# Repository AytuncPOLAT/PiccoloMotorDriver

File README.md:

# PiccoloMotorDriver

Yet another open source servo motor driver designed using Kicad, based on STM32H723 MCU and DRV8316 integrated 3-phase motor driver.

Firmware can be found here (under development): https://github.com/AytuncPOLAT/PiccoloMotorDriverFw

All the subsystems have been tested

| Subsystem     | Test Status           |
| ---------     | ------------------    |
| FDCAN         | :heavy_check_mark:    |
| RS485         | :heavy_check_mark:    |
| USB           | :heavy_check_mark:    |
| Debug UART    | :clock9:              |
| SWD           | :heavy_check_mark:    |
| Ext. Encoder  | :heavy_check_mark:    |
| Ext. Analog   | :heavy_check_mark:    |
| LEDs          | :heavy_check_mark:    |
| J9 GPIOs      | :clock9:              |
| DRV8316       | :heavy_check_mark:    |

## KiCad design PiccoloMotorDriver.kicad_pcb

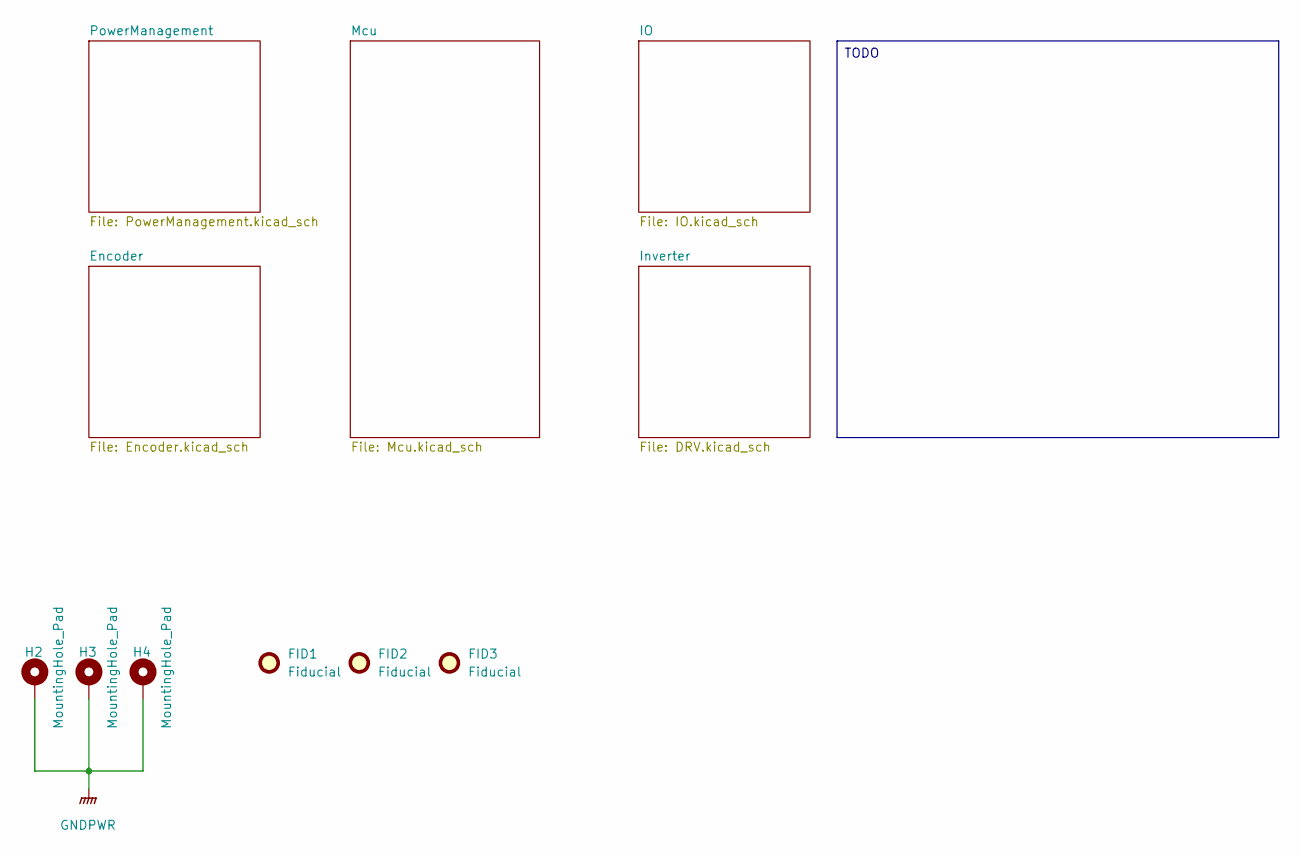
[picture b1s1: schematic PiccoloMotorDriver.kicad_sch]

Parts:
FID1, FID2, FID3: Fiducial; Fiducial_0.5mm_Mask1mm
H2, H3, H4: MountingHole_Pad; MountingHole_3.2mm_M3_Pad_Via

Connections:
GND: H2.1 (1_1), H3.1 (1_1), H4.1 (1_1); also elsewhere on the board

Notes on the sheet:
TODO

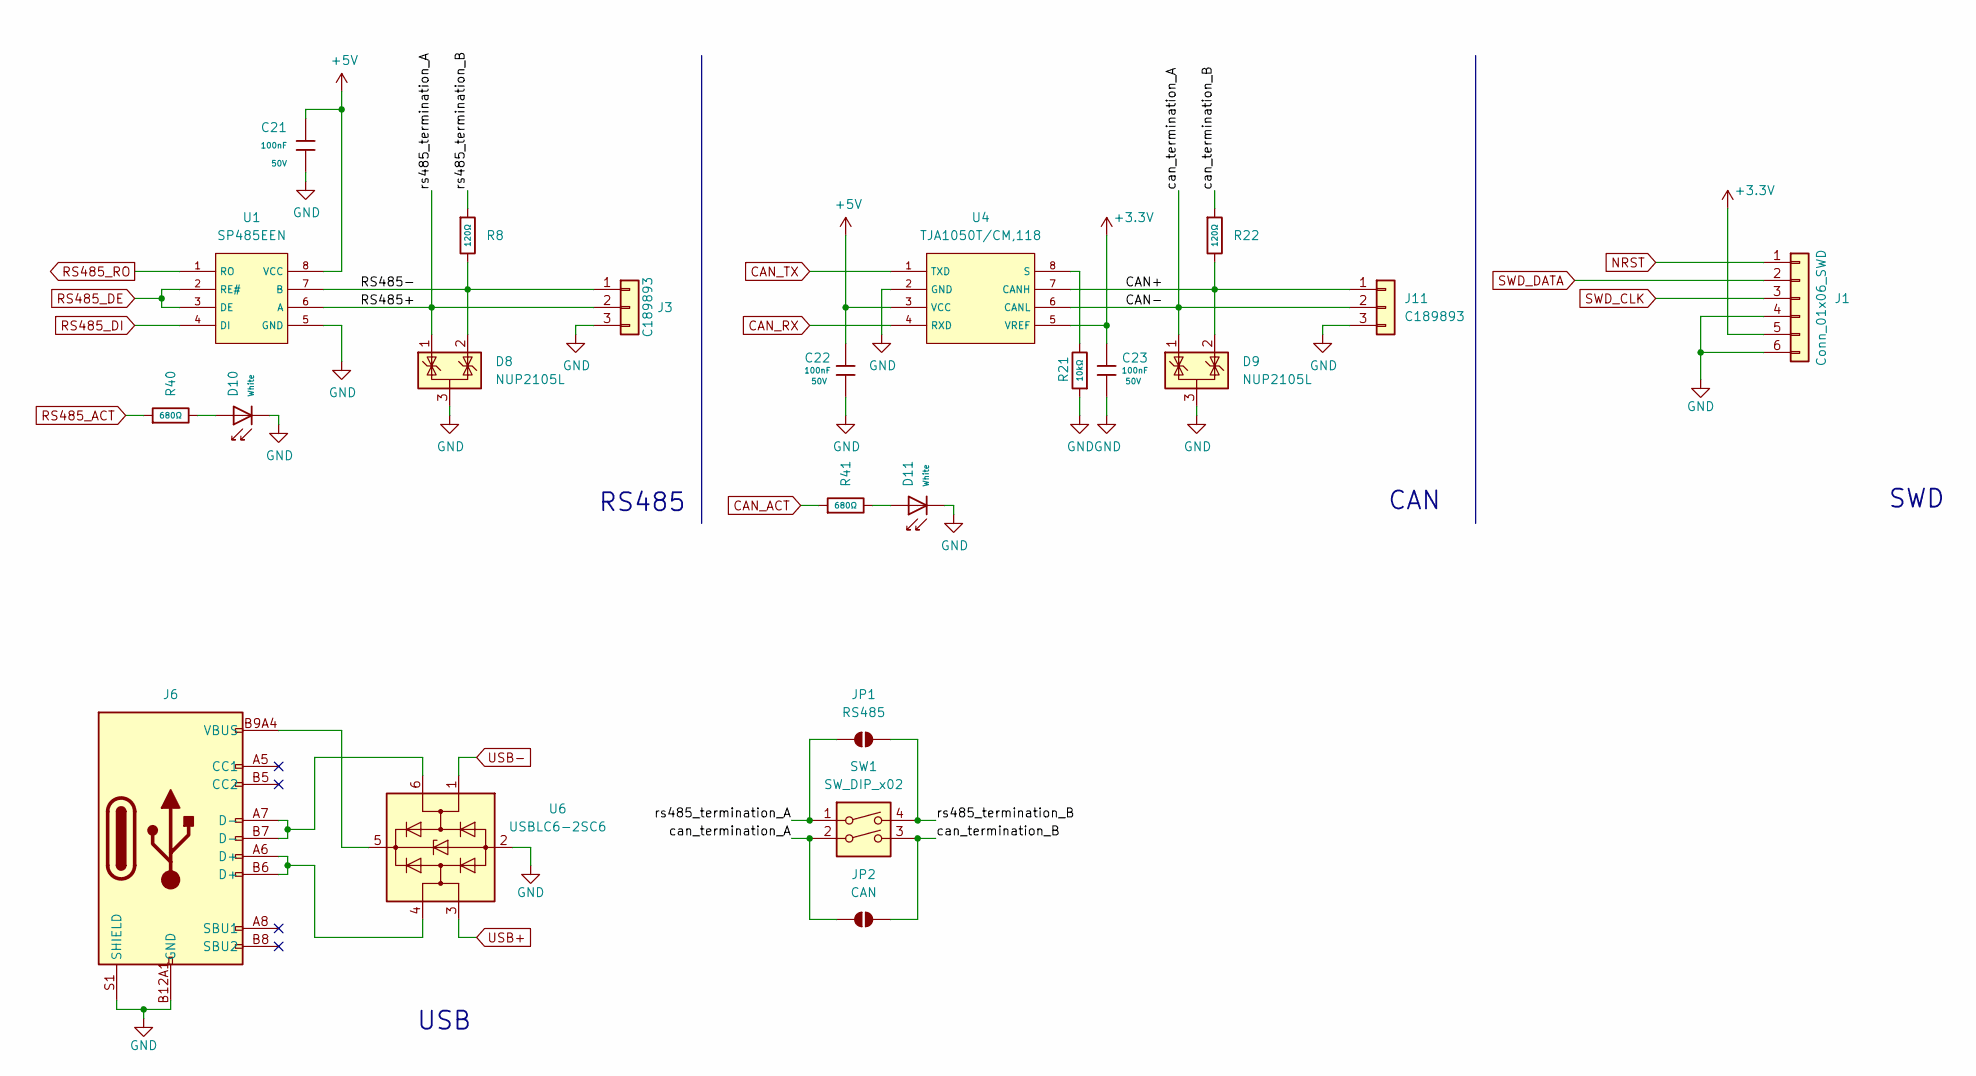
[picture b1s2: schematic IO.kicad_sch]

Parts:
C21, C22, C23: 100nF; C_0603; Voltage Rated 50V; Tolerance ±10%; Part CC0603KRX7R9BB104; LCSC C14663
D8, D9: NUP2105L; SOT-23; LCSC C14486
D10, D11: White; D_0603; Part KT-0603W; LCSC C2290
J1: Conn_01x06_SWD; JST_GH_SM05B-GHS-TB_1x05-1MP_P1.25mm_Horizontal; LCSC C189896
J3, J11: C189893; JST_GH_SM02B-GHS-TB_1x02-1MP_P1.25mm_Horizontal; LCSC C189893
J6: Connector, USB-TYPE-C-16P; TYPE-C-SMD_HX-TYPE-C-16PIN; LCSC C2927039
JP1: RS485; SolderJumper-2_P1.3mm_Open_TrianglePad1.0x1.5mm
JP2: CAN; SolderJumper-2_P1.3mm_Open_TrianglePad1.0x1.5mm
R8, R22: 120Ω; R_0603; Overload Voltage (Max) 75V; Tolerance ±1%; Part 0603WAF1200T5E; LCSC C22787
R21: 10kΩ; R_0603; Overload Voltage (Max) 75V; Tolerance ±1%; Part 0603WAF1002T5E; LCSC C25804
R40, R41: 680Ω; R_0603; Overload Voltage (Max) 75V; Tolerance ±1%; Part 0603WAF6800T5E; LCSC C23228
SW1: SW_DIP_x02; SMDIP-4_W7.62mm; LCSC C6331180
U1: SP485EEN; SOIC-8_L5.0-W4.0-P1.27-LS6.0-BL; Supply Voltage 4.75V~5.25V; Part SP485EEN-L/TR; LCSC C6855
U4: TJA1050T/CM,118; SOIC-8_L5.0-W4.0-P1.27-LS6.0-BL; Supply Voltage 4.75V~5.25V; Part TJA1050T/CM,118; LCSC C6952
U6: USBLC6-2SC6; SOT-23-6; LCSC C5261088

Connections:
+3.3V: C23.1, J1.5, U4.5 (VREF); also elsewhere on the board
+5V: C21.1, C22.1, U1.8 (VCC), U4.3 (VCC); also elsewhere on the board
/IO/CAN+: D9.2 (K), J11.1, R22.2, U4.7 (CANH)
/IO/CAN-: D9.1 (K), J11.2, JP2.1 (A), SW1.2, U4.6 (CANL)
/IO/RS485+: D8.1 (K), J3.2, JP1.2 (B), SW1.1, U1.6 (A)
/IO/RS485-: D8.2 (K), J3.1, R8.2, U1.7 (B)
/IO/can_termination_B: JP2.2 (B), R22.1, SW1.3
/IO/rs485_termination_B: JP1.1 (A), R8.1, SW1.4
CAN_ACT: R41.1; also elsewhere on the board
CAN_RX: U4.4 (RXD); also elsewhere on the board
CAN_TX: U4.1 (TXD); also elsewhere on the board
GND: C21.2, C22.2, C23.2, D8.3 (A), D9.3 (A), D10.1, D11.1, J1.4, J1.6, J3.3, J6.A12B1 (GND), J6.B12A1 (GND), J6.S1 (SHIELD), J11.3, R21.1, U1.5 (GND), U4.2 (GND), U6.2 (GND); also elsewhere on the board
NRST: J1.1; also elsewhere on the board
unnamed: D10.2, R40.2
unnamed: D11.2, R41.2
unnamed: J6.A6 (D+), J6.B6 (D+), U6.4 (I/O2)
unnamed: J6.A7 (D-), J6.B7 (D-), U6.6 (I/O1)
unnamed: R21.2, U4.8 (S)
unnamed: J6.A9B4 (VBUS), J6.B9A4 (VBUS), U6.5 (VBUS)
RS485_ACT: R40.1; also elsewhere on the board
RS485_DE: U1.2 (RE#), U1.3 (DE); also elsewhere on the board
RS485_DI: U1.4 (DI); also elsewhere on the board
RS485_RO: U1.1 (RO); also elsewhere on the board
SWD_CLK: J1.3; also elsewhere on the board
SWD_DATA: J1.2; also elsewhere on the board
USB+: U6.3 (I/O2); also elsewhere on the board
USB-: U6.1 (I/O1); also elsewhere on the board

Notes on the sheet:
RS485
USB
SWD
CAN

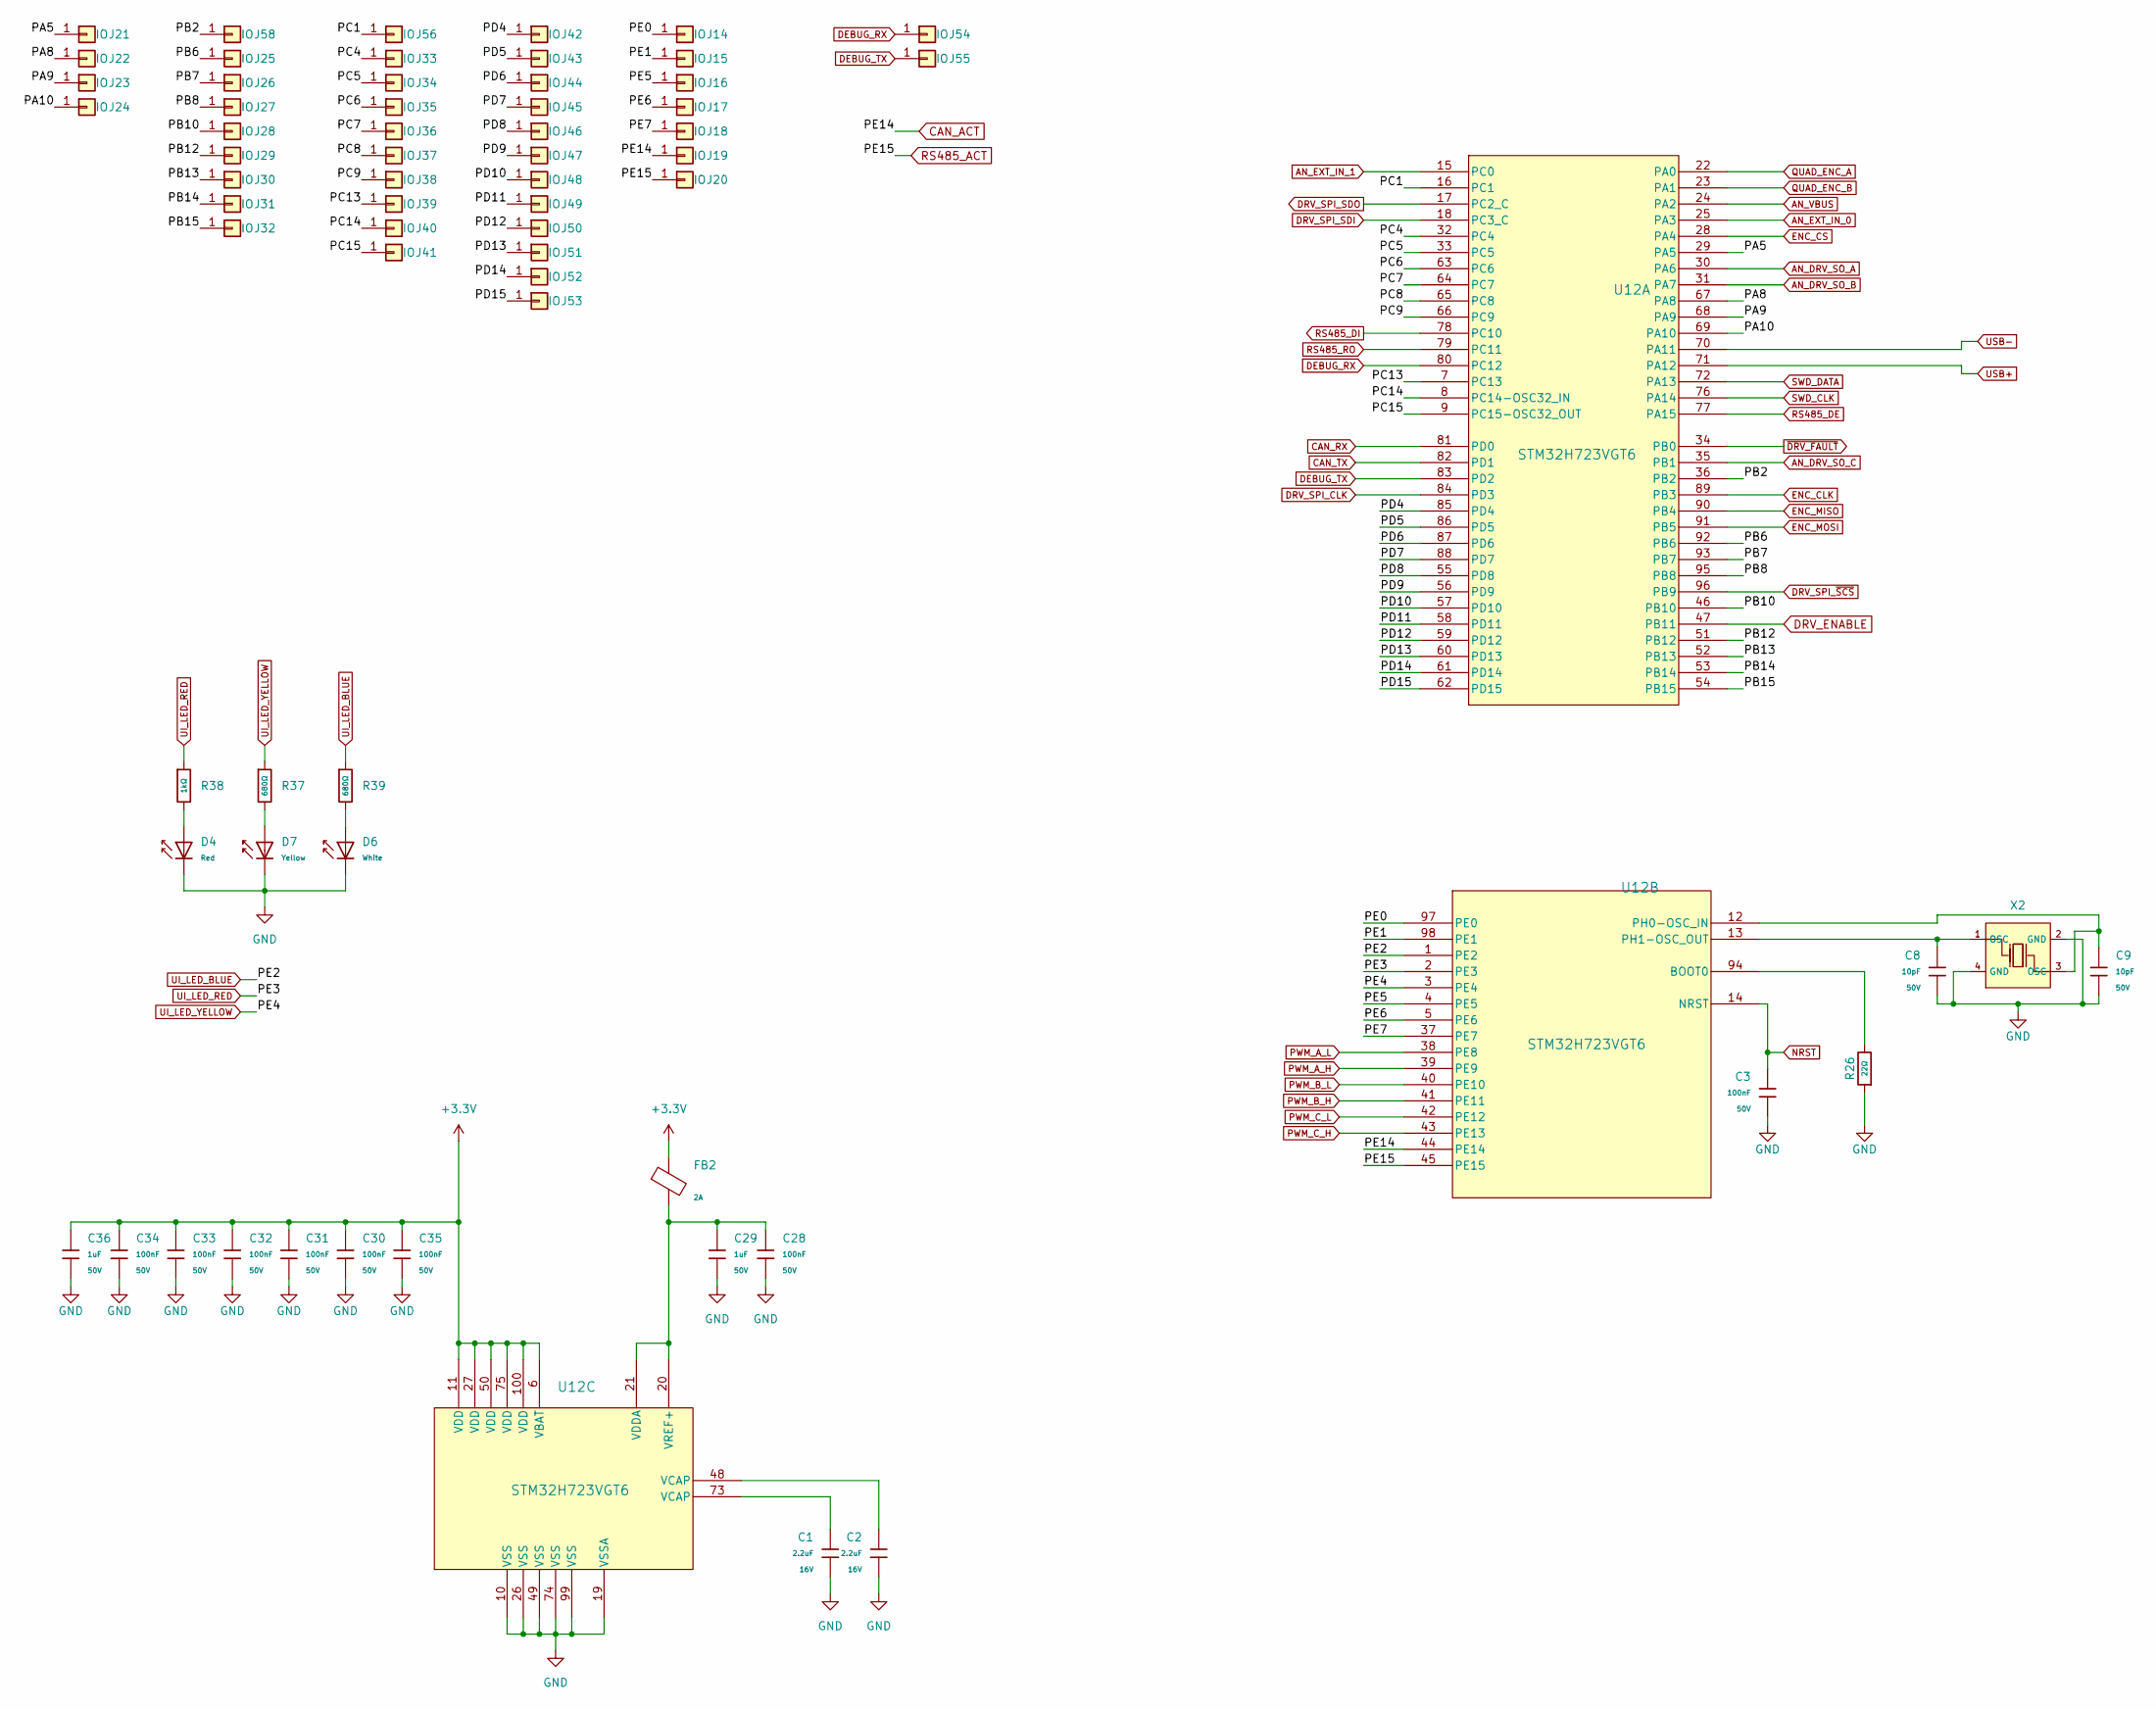
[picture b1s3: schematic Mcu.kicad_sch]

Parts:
C1, C2: 2.2uF; C_0603; Voltage Rated 16V; Tolerance ±10%; Part CL10A225KO8NNNC; LCSC C23630
C3, C28, C30, C31, C32, C33, C34, C35: 100nF; C_0603; Voltage Rated 50V; Tolerance ±10%; Part CC0603KRX7R9BB104; LCSC C14663
C8, C9: 10pF; C_0603; Voltage Rated 50V; Tolerance ±5%; Part CL10C100JB8NNNC; LCSC C1634
C29, C36: 1uF; C_0603; Voltage Rated 50V; Tolerance ±10%; Part CL10A105KB8NNNC; LCSC C15849
D4: Red; D_0603; Part KT-0603R; LCSC C2286
D6: White; D_0603; Part KT-0603W; LCSC C2290
D7: Yellow; D_0603; Forward Voltage (VF) 1.6V~2.6V; Part NCD0603Y2; LCSC C89811
FB2: FB_0603; Current Rating 2A; Tolerance ±25%; Part BLM18PG121SN1D; LCSC C14709
J14, J15, J16, J17, J18, J19, J20, J21, J22, J23, J24, J25, J26, J27, J28, J29, J30, J31, J32, J33, J34, J35, J36, J37, J38, J39, J40, J41, J42, J43, J44, J45, J46, J47, J48, J49, J50, J51, J52, J53, J54, J55, J56, J58: IO; TestPoint_THTPad_D1.0mm_Drill0.5mm
R26: 22Ω; R_0603; Overload Voltage (Max) 75V; Tolerance ±1%; Part 0603WAF220JT5E; LCSC C23345
R37, R39: 680Ω; R_0603; Overload Voltage (Max) 75V; Tolerance ±1%; Part 0603WAF6800T5E; LCSC C23228
R38: 1kΩ; R_0603; Overload Voltage (Max) 75V; Tolerance ±1%; Part 0603WAF1001T5E; LCSC C21190
U12: STM32H723VGT6; LQFP-100_14x14mm_P0.5mm; LCSC C730142
X2: X322516MLB4SI; OSC-SMD_4P-L3.2-W2.5-BL; Frequency Tolerance ±10ppm; Part X322516MLB4SI; LCSC C13738

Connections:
+3.3V: C30.1, C31.1, C32.1, C33.1, C34.1, C35.1, C36.1, FB2.1, U12.6 (VBAT), U12.11 (VDD), U12.27 (VDD), U12.50 (VDD), U12.75 (VDD), U12.100 (VDD); also elsewhere on the board
/Mcu/PA5: J21.1 (Pin_1_1), U12.29 (PA5)
/Mcu/PA8: J22.1 (Pin_1_1), U12.67 (PA8)
/Mcu/PA9: J23.1 (Pin_1_1), U12.68 (PA9)
/Mcu/PA10: J24.1 (Pin_1_1), U12.69 (PA10)
/Mcu/PB2: J58.1 (Pin_1_1), U12.36 (PB2)
/Mcu/PB6: J25.1 (Pin_1_1), U12.92 (PB6)
/Mcu/PB7: J26.1 (Pin_1_1), U12.93 (PB7)
/Mcu/PB8: J27.1 (Pin_1_1), U12.95 (PB8)
/Mcu/PB10: J28.1 (Pin_1_1), U12.46 (PB10)
/Mcu/PB12: J29.1 (Pin_1_1), U12.51 (PB12)
/Mcu/PB13: J30.1 (Pin_1_1), U12.52 (PB13)
/Mcu/PB14: J31.1 (Pin_1_1), U12.53 (PB14)
/Mcu/PB15: J32.1 (Pin_1_1), U12.54 (PB15)
/Mcu/PC1: J56.1 (Pin_1_1), U12.16 (PC1)
/Mcu/PC4: J33.1 (Pin_1_1), U12.32 (PC4)
/Mcu/PC5: J34.1 (Pin_1_1), U12.33 (PC5)
/Mcu/PC6: J35.1 (Pin_1_1), U12.63 (PC6)
/Mcu/PC7: J36.1 (Pin_1_1), U12.64 (PC7)
/Mcu/PC8: J37.1 (Pin_1_1), U12.65 (PC8)
/Mcu/PC9: J38.1 (Pin_1_1), U12.66 (PC9)
/Mcu/PC13: J39.1 (Pin_1_1), U12.7 (PC13)
/Mcu/PC14: J40.1 (Pin_1_1), U12.8 (PC14-OSC32_IN)
/Mcu/PC15: J41.1 (Pin_1_1), U12.9 (PC15-OSC32_OUT)
/Mcu/PD4: J42.1 (Pin_1_1), U12.85 (PD4)
/Mcu/PD5: J43.1 (Pin_1_1), U12.86 (PD5)
/Mcu/PD6: J44.1 (Pin_1_1), U12.87 (PD6)
/Mcu/PD7: J45.1 (Pin_1_1), U12.88 (PD7)
/Mcu/PD8: J46.1 (Pin_1_1), U12.55 (PD8)
/Mcu/PD9: J47.1 (Pin_1_1), U12.56 (PD9)
/Mcu/PD10: J48.1 (Pin_1_1), U12.57 (PD10)
/Mcu/PD11: J49.1 (Pin_1_1), U12.58 (PD11)
/Mcu/PD12: J50.1 (Pin_1_1), U12.59 (PD12)
/Mcu/PD13: J51.1 (Pin_1_1), U12.60 (PD13)
/Mcu/PD14: J52.1 (Pin_1_1), U12.61 (PD14)
/Mcu/PD15: J53.1 (Pin_1_1), U12.62 (PD15)
/Mcu/PE0: J14.1 (Pin_1_1), U12.97 (PE0)
/Mcu/PE1: J15.1 (Pin_1_1), U12.98 (PE1)
/Mcu/PE5: J16.1 (Pin_1_1), U12.4 (PE5)
/Mcu/PE6: J17.1 (Pin_1_1), U12.5 (PE6)
/Mcu/PE7: J18.1 (Pin_1_1), U12.37 (PE7)
AN_DRV_SO_A: U12.30 (PA6); also elsewhere on the board
AN_DRV_SO_B: U12.31 (PA7); also elsewhere on the board
AN_DRV_SO_C: U12.35 (PB1); also elsewhere on the board
AN_EXT_IN_0: U12.25 (PA3); also elsewhere on the board
AN_EXT_IN_1: U12.15 (PC0); also elsewhere on the board
AN_VBUS: U12.24 (PA2); also elsewhere on the board
CAN_ACT: J19.1 (Pin_1_1), U12.44 (PE14); also elsewhere on the board
CAN_RX: U12.81 (PD0); also elsewhere on the board
CAN_TX: U12.82 (PD1); also elsewhere on the board
DEBUG_RX: J54.1 (Pin_1_1), U12.80 (PC12)
DEBUG_TX: J55.1 (Pin_1_1), U12.83 (PD2)
DRV_ENABLE: U12.47 (PB11); also elsewhere on the board
DRV_SPI_CLK: U12.84 (PD3); also elsewhere on the board
DRV_SPI_SDI: U12.18 (PC3_C); also elsewhere on the board
DRV_SPI_SDO: U12.17 (PC2_C); also elsewhere on the board
DRV_SPI_~SCS: U12.96 (PB9); also elsewhere on the board
ENC_CLK: U12.89 (PB3); also elsewhere on the board
ENC_CS: U12.28 (PA4); also elsewhere on the board
ENC_MISO: U12.90 (PB4); also elsewhere on the board
ENC_MOSI: U12.91 (PB5); also elsewhere on the board
GND: C1.2, C2.2, C3.2, C8.2, C9.2, C28.2, C29.2, C30.2, C31.2, C32.2, C33.2, C34.2, C35.2, C36.2, D4.1, D6.1, D7.1, R26.1, U12.10 (VSS), U12.19 (VSSA), U12.26 (VSS), U12.49 (VSS), U12.74 (VSS), U12.99 (VSS), X2.2 (GND), X2.4 (GND); also elsewhere on the board
NRST: C3.1, U12.14 (NRST); also elsewhere on the board
unnamed: C1.1, U12.73 (VCAP)
unnamed: C2.1, U12.48 (VCAP)
unnamed: D4.2, R38.2
unnamed: D6.2, R39.2
unnamed: D7.2, R37.2
unnamed: R26.2, U12.94 (BOOT0)
unnamed: C9.1, U12.12 (PH0-OSC_IN), X2.3 (OSC)
unnamed: C8.1, U12.13 (PH1-OSC_OUT), X2.1 (OSC)
unnamed: C28.1, C29.1, FB2.2, U12.20 (VREF+), U12.21 (VDDA)
PWM_A_H: U12.39 (PE9); also elsewhere on the board
PWM_A_L: U12.38 (PE8); also elsewhere on the board
PWM_B_H: U12.41 (PE11); also elsewhere on the board
PWM_B_L: U12.40 (PE10); also elsewhere on the board
PWM_C_H: U12.43 (PE13); also elsewhere on the board
PWM_C_L: U12.42 (PE12); also elsewhere on the board
QUAD_ENC_A: U12.22 (PA0); also elsewhere on the board
QUAD_ENC_B: U12.23 (PA1); also elsewhere on the board
RS485_ACT: J20.1 (Pin_1_1), U12.45 (PE15); also elsewhere on the board
RS485_DE: U12.77 (PA15); also elsewhere on the board
RS485_DI: U12.78 (PC10); also elsewhere on the board
RS485_RO: U12.79 (PC11); also elsewhere on the board
SWD_CLK: U12.76 (PA14); also elsewhere on the board
SWD_DATA: U12.72 (PA13); also elsewhere on the board
UI_LED_BLUE: R39.1, U12.1 (PE2)
UI_LED_RED: R38.1, U12.2 (PE3)
UI_LED_YELLOW: R37.1, U12.3 (PE4)
USB+: U12.71 (PA12); also elsewhere on the board
USB-: U12.70 (PA11); also elsewhere on the board
~DRV_FAULT: U12.34 (PB0); also elsewhere on the board

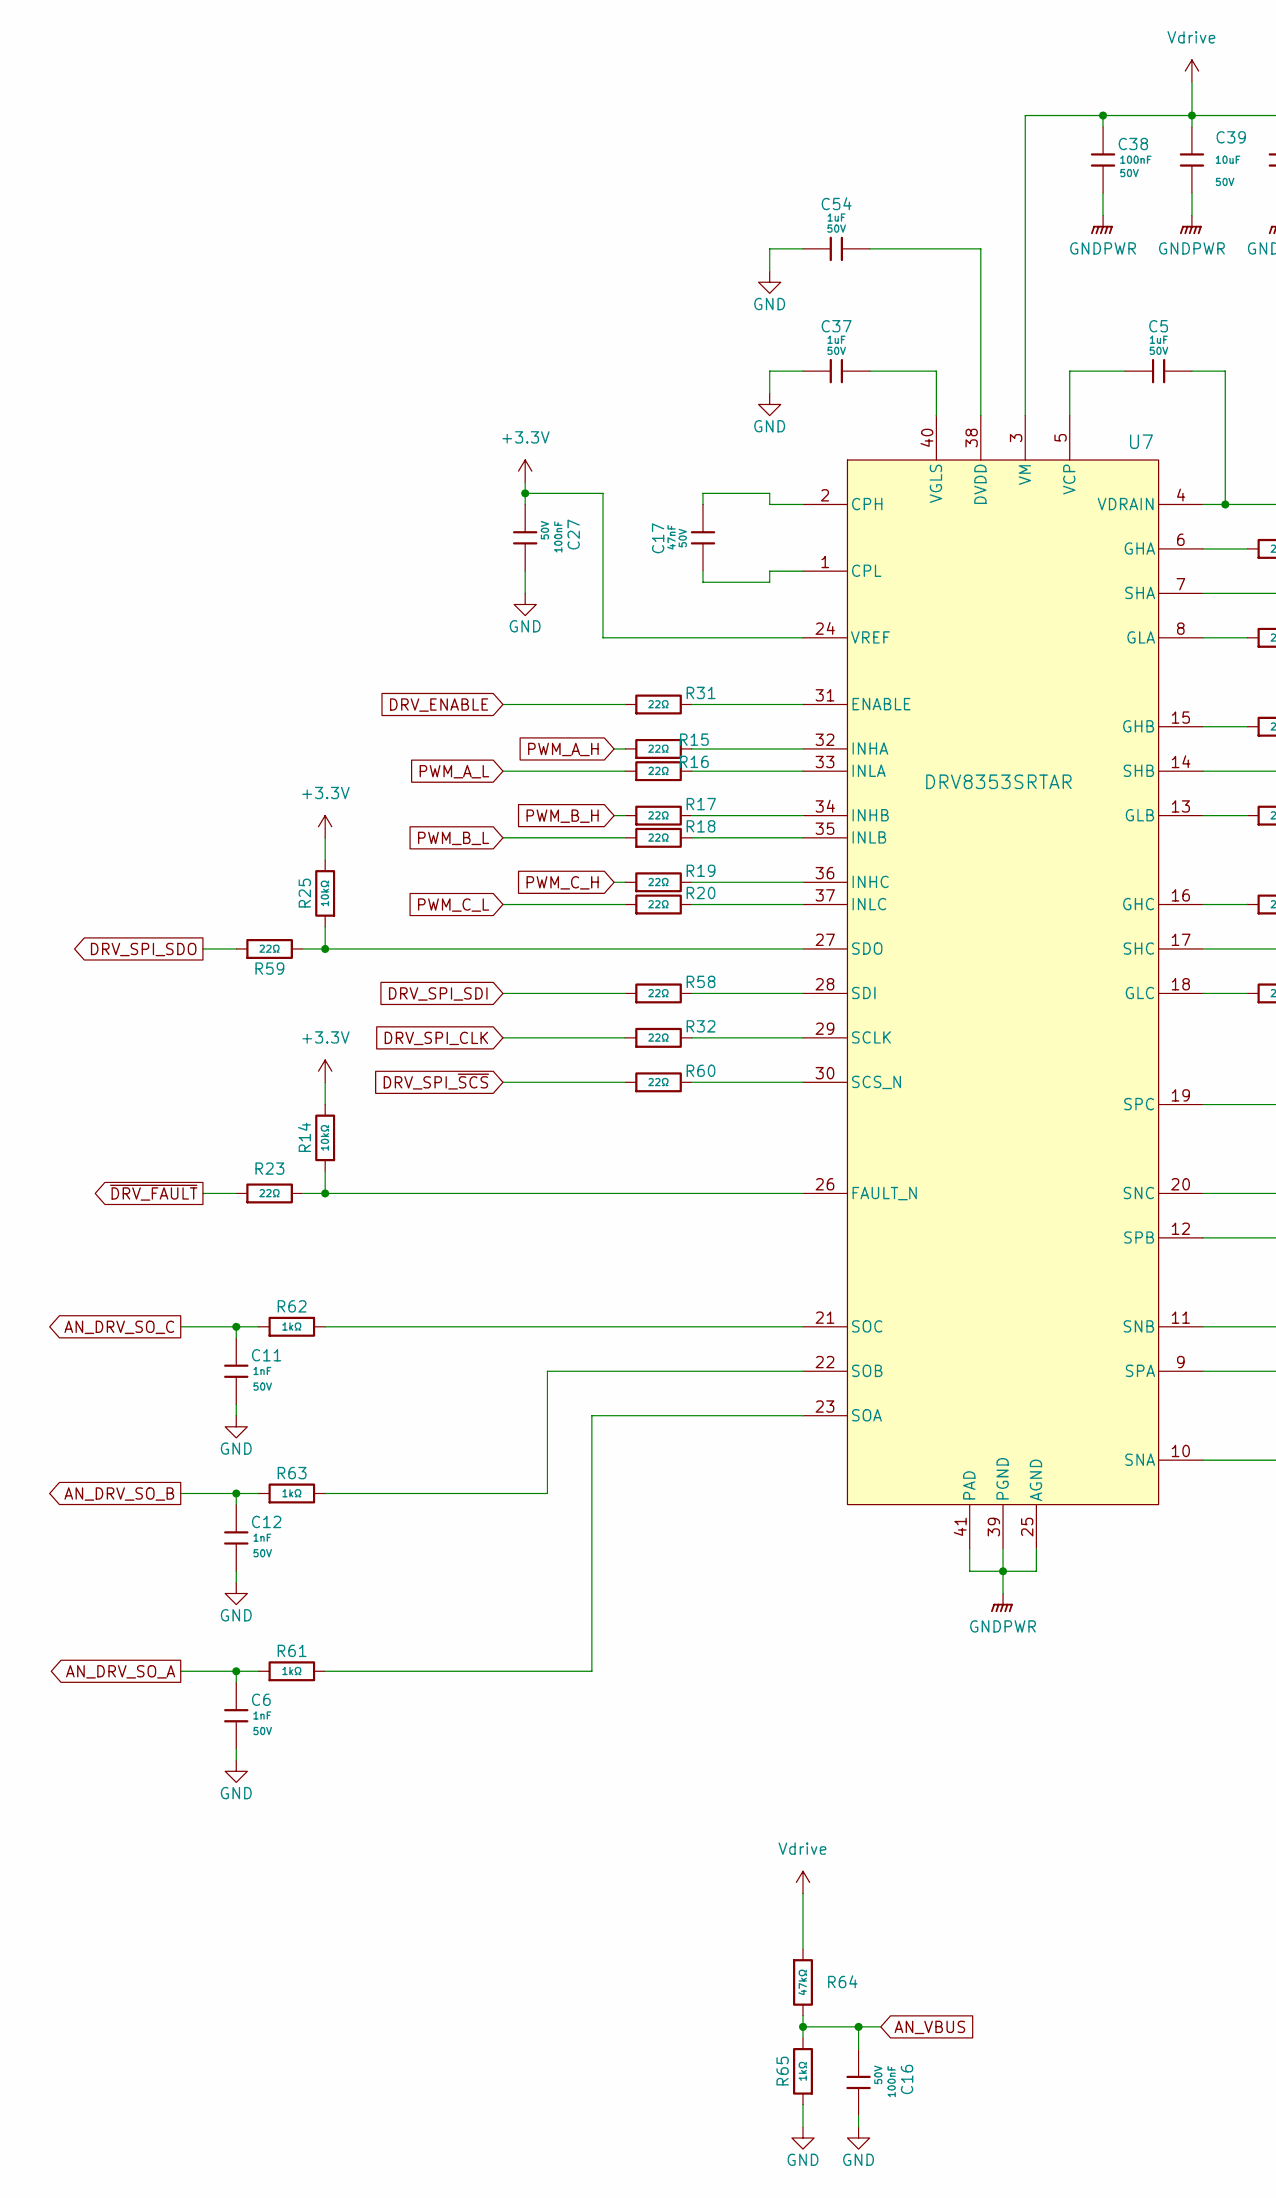
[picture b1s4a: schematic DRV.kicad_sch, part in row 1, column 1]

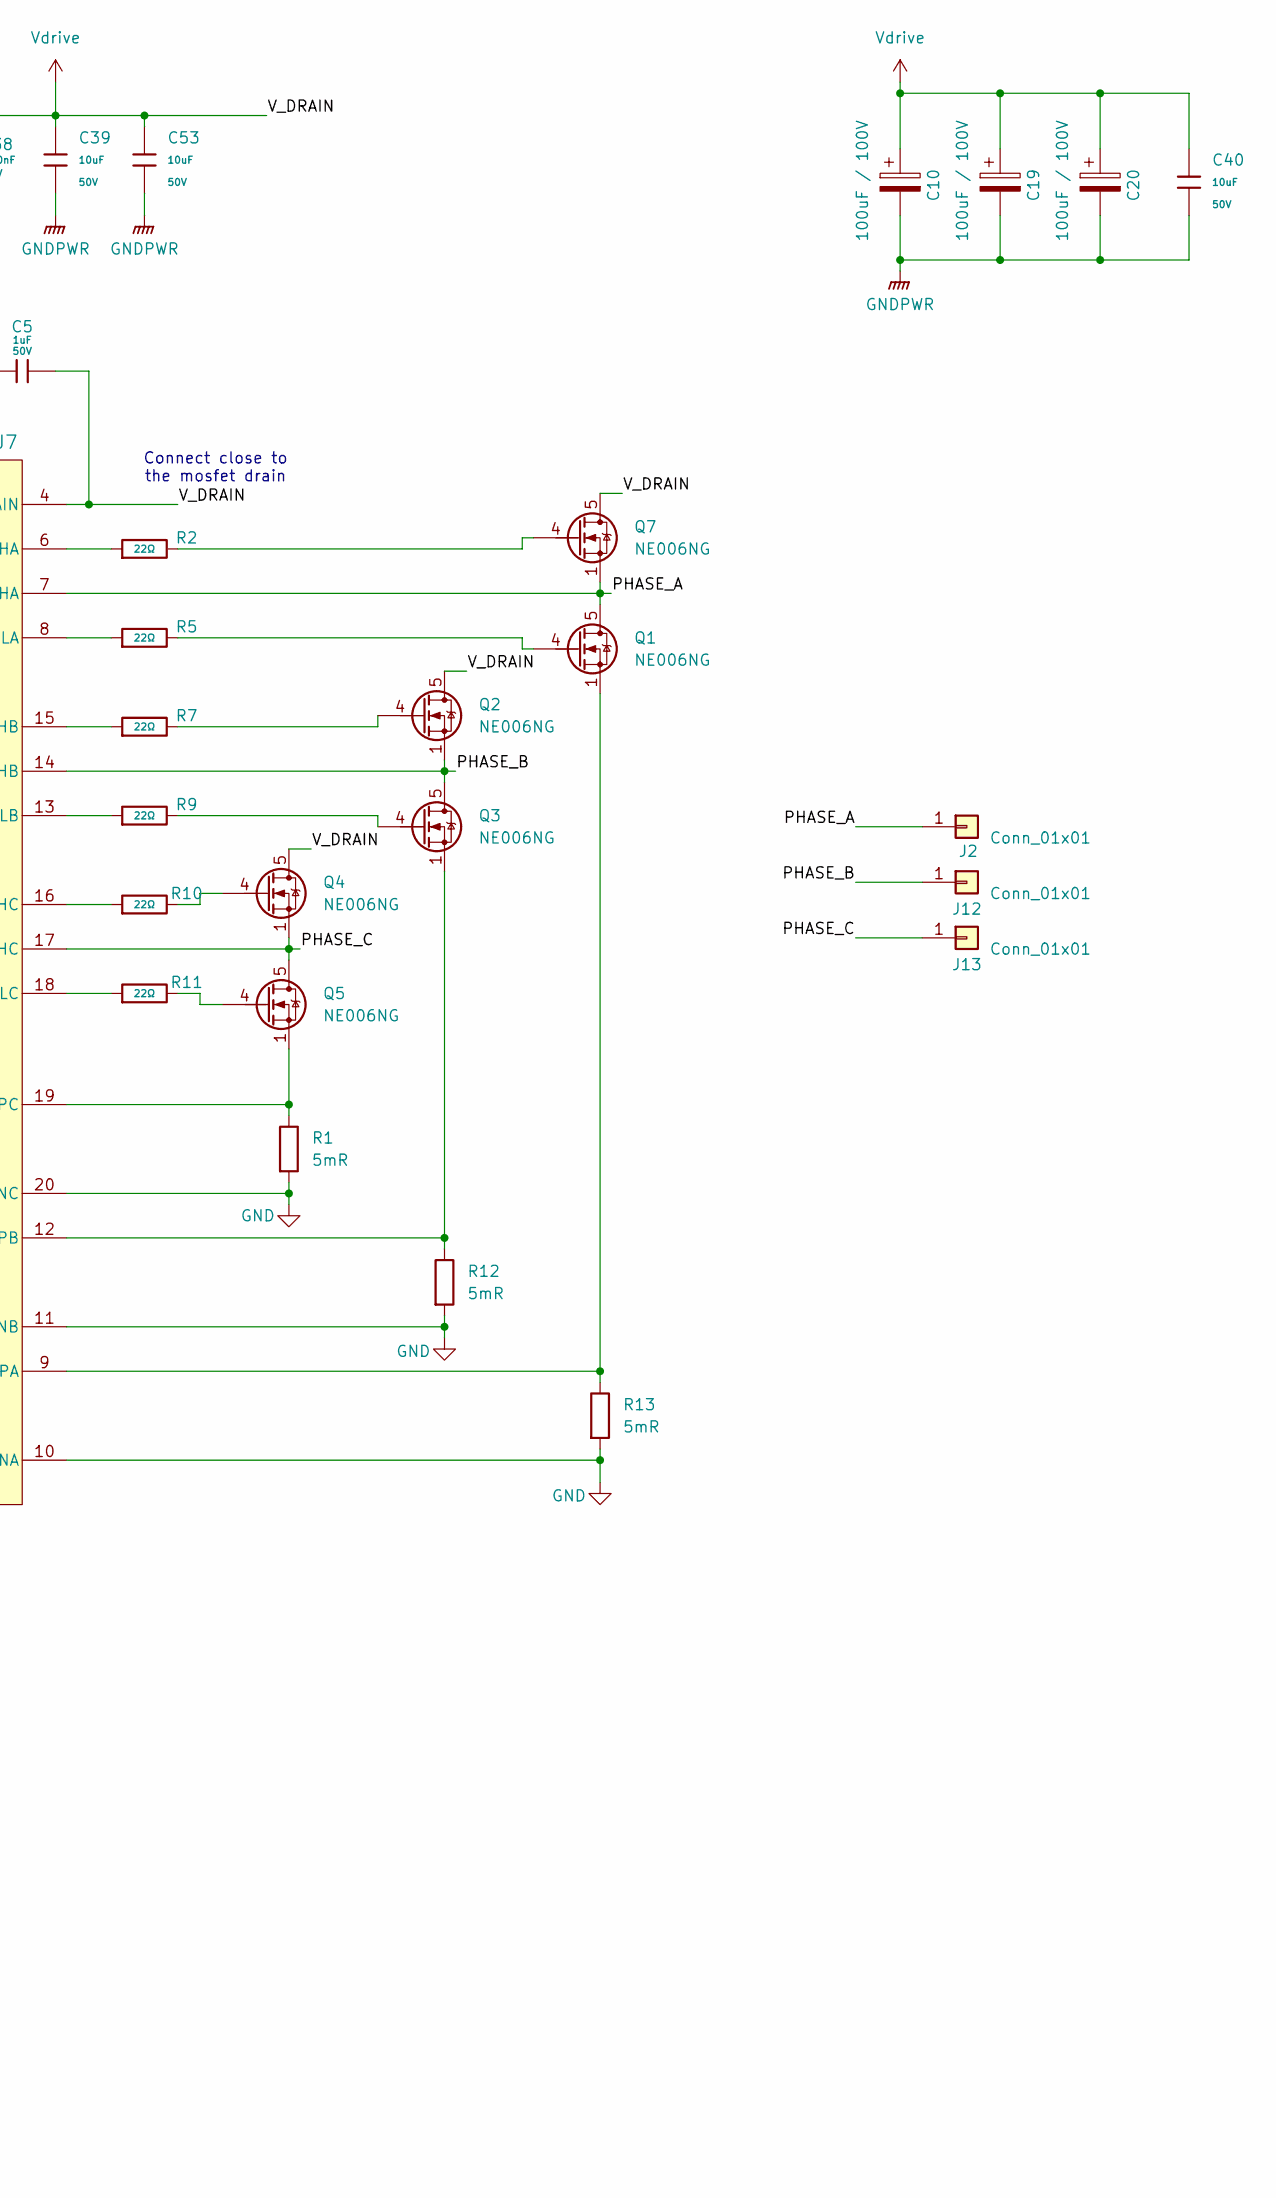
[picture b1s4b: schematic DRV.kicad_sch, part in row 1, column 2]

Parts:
C5, C37, C54: 1uF; C_0603; Voltage Rated 50V; Tolerance ±10%; Part CL10A105KB8NNNC; LCSC C15849
C6, C11, C12: 1nF; C_0603; Voltage Rated 50V; Tolerance ±10%; Part CL10B102KB8NNNC; LCSC C1588
C10, C19, C20: 100uF / 100V; CP_Elec_10x10.5; LCSC C3008502
C16, C27, C38: 100nF; C_0603; Voltage Rated 50V; Tolerance ±10%; Part CC0603KRX7R9BB104; LCSC C14663
C17: 47nF; C_0603; Voltage Rated 50V; Tolerance ±10%; Part CL10B473KB8NNNC; LCSC C1622
C39, C40, C53: 10uF; C_1206; Voltage Rated 50V; Tolerance ±10%; Part CL31A106KBHNNNE; LCSC C13585
J2, J12, J13: Conn_01x01; SolderWire-2.5sqmm_1x01_D2.4mm_OD3.6mm
Q1, Q2, Q3, Q4, Q5, Q7: NE006NG; AO_DFN-8-1EP_5.55x5.2mm_P1.27mm_EP4.12x4.6mm; LCSC C54157801
R1, R12, R13: 5mR; R_2512_6332Metric; LCSC C41382686
R2, R5, R7, R9, R10, R11, R15, R16, R17, R18, R19, R20, R23, R31, R32, R58, R59, R60: 22Ω; R_0603; Overload Voltage (Max) 75V; Tolerance ±1%; Part 0603WAF220JT5E; LCSC C23345
R14, R25: 10kΩ; R_0603; Overload Voltage (Max) 75V; Tolerance ±1%; Part 0603WAF1002T5E; LCSC C25804
R61, R62, R63, R65: 1kΩ; R_0603; Overload Voltage (Max) 75V; Tolerance ±1%; Part 0603WAF1001T5E; LCSC C21190
R64: 47kΩ; R_0603; Overload Voltage (Max) 75V; Tolerance ±1%; Part 0603WAF4702T5E; LCSC C25819
U7: DRV8353SRTAR; RTA0040B; LCSC C701785

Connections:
+3.3V: C27.1, R14.2, R25.2, U7.24 (VREF); also elsewhere on the board
/Inverter/PHASE_A: J2.1 (Pin_1_1), Q1.5 (D), Q7.1 (S), Q7.2 (S), Q7.3 (S), U7.7 (SHA)
/Inverter/PHASE_B: J12.1 (Pin_1_1), Q2.1 (S), Q2.2 (S), Q2.3 (S), Q3.5 (D), U7.14 (SHB)
/Inverter/PHASE_C: J13.1 (Pin_1_1), Q4.1 (S), Q4.2 (S), Q4.3 (S), Q5.5 (D), U7.17 (SHC)
AN_DRV_SO_A: C6.1, R61.1; also elsewhere on the board
AN_DRV_SO_B: C12.1, R63.1; also elsewhere on the board
AN_DRV_SO_C: C11.1, R62.1; also elsewhere on the board
AN_VBUS: C16.1, R64.2, R65.2; also elsewhere on the board
DRV_ENABLE: R31.1; also elsewhere on the board
DRV_SPI_CLK: R32.1; also elsewhere on the board
DRV_SPI_SDI: R58.1; also elsewhere on the board
DRV_SPI_SDO: R59.1; also elsewhere on the board
DRV_SPI_~SCS: R60.1; also elsewhere on the board
GND: C6.2, C10.2, C11.2, C12.2, C16.2, C19.2, C20.2, C27.2, C37.1, C38.2, C39.2, C40.2, C53.2, C54.1, R1.2, R12.2, R13.2, R65.1, U7.10 (SNA), U7.11 (SNB), U7.20 (SNC), U7.25 (AGND), U7.39 (PGND), U7.41 (PAD); also elsewhere on the board
unnamed: Q1.4 (G), R5.2
unnamed: Q2.4 (G), R7.2
unnamed: Q3.4 (G), R9.2
unnamed: Q4.4 (G), R10.2
unnamed: Q5.4 (G), R11.2
unnamed: Q7.4 (G), R2.2
unnamed: C17.2, U7.2 (CPH)
unnamed: C17.1, U7.1 (CPL)
unnamed: C54.2, U7.38 (DVDD)
unnamed: R31.2, U7.31 (ENABLE)
unnamed: R14.1, R23.2, U7.26 (FAULT_N)
unnamed: R2.1, U7.6 (GHA)
unnamed: R7.1, U7.15 (GHB)
unnamed: R10.1, U7.16 (GHC)
unnamed: R5.1, U7.8 (GLA)
unnamed: R9.1, U7.13 (GLB)
unnamed: R11.1, U7.18 (GLC)
unnamed: R15.2, U7.32 (INHA)
unnamed: R17.2, U7.34 (INHB)
unnamed: R19.2, U7.36 (INHC)
unnamed: R16.2, U7.33 (INLA)
unnamed: R18.2, U7.35 (INLB)
unnamed: R20.2, U7.37 (INLC)
unnamed: R32.2, U7.29 (SCLK)
unnamed: R60.2, U7.30 (SCS_N)
unnamed: R58.2, U7.28 (SDI)
unnamed: R25.1, R59.2, U7.27 (SDO)
unnamed: R61.2, U7.23 (SOA)
unnamed: R63.2, U7.22 (SOB)
unnamed: R62.2, U7.21 (SOC)
unnamed: Q1.1 (S), Q1.2 (S), Q1.3 (S), R13.1, U7.9 (SPA)
unnamed: Q3.1 (S), Q3.2 (S), Q3.3 (S), R12.1, U7.12 (SPB)
unnamed: Q5.1 (S), Q5.2 (S), Q5.3 (S), R1.1, U7.19 (SPC)
unnamed: C5.1, U7.5 (VCP)
unnamed: C37.2, U7.40 (VGLS)
PWM_A_H: R15.1; also elsewhere on the board
PWM_A_L: R16.1; also elsewhere on the board
PWM_B_H: R17.1; also elsewhere on the board
PWM_B_L: R18.1; also elsewhere on the board
PWM_C_H: R19.1; also elsewhere on the board
PWM_C_L: R20.1; also elsewhere on the board
Vdrive: C5.2, C10.1, C19.1, C20.1, C38.1, C39.1, C40.1, C53.1, Q2.5 (D), Q4.5 (D), Q7.5 (D), R64.1, U7.3 (VM), U7.4 (VDRAIN); also elsewhere on the board
~DRV_FAULT: R23.1; also elsewhere on the board

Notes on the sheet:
Connect close to the mosfet drain
